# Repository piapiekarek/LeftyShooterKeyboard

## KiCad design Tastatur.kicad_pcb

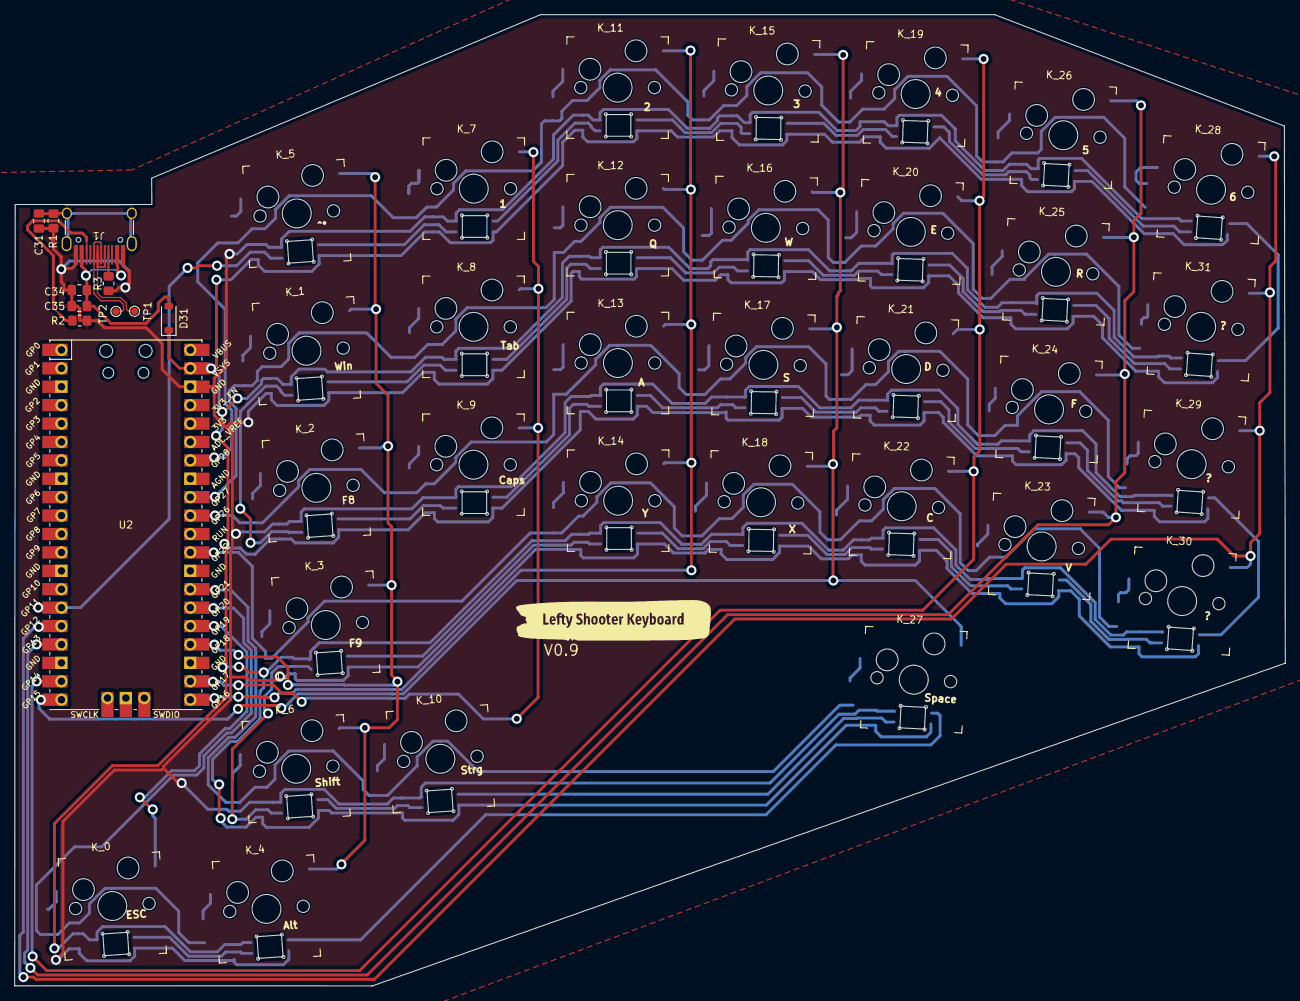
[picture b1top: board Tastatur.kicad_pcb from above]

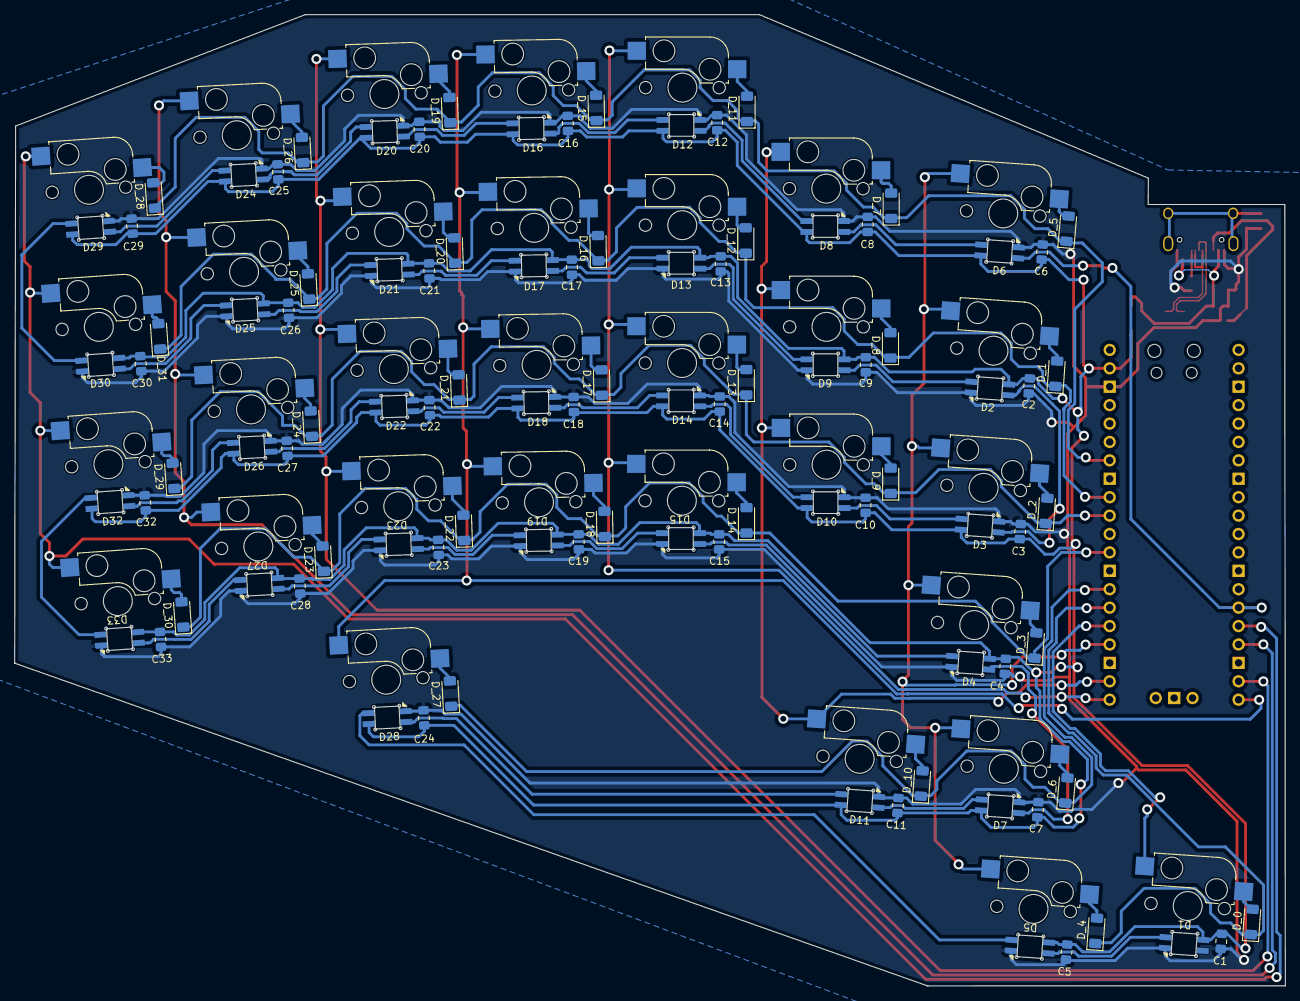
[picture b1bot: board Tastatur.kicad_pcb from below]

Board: 2 copper layers, 175.3 x 134.0 mm, 139 parts (96 on the bottom side), 56 nets.

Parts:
C1, C2, C3, C4, C5, C6, C7, C8, C9, C10, C11, C12, C13, C14, C15, C16, C17, C18, C19, C20, C21, C22, C23, C24, C25, C26, C27, C28, C29, C30, C32, C33, C35: 100n; C_0805_2012Metric_Pad1.18x1.45mm_HandSolder
C31: 20pF; C_0805_2012Metric_Pad1.18x1.45mm_HandSolder
C34: 1u; C_0805_2012Metric_Pad1.18x1.45mm_HandSolder
D1, D2, D3, D4, D5, D6, D7, D8, D9, D10, D11, D12, D13, D14, D15, D16, D17, D18, D19, D20, D21, D22, D23, D24, D25, D26, D27, D28, D29, D30, D32, D33: SK6812MINI; SK6803-MINI-E_pia
D31: 1N5817; D_SOD-123
D_0, D_1, D_2, D_3, D_4, D_5, D_6, D_7, D_8, D_9, D_10, D_11, D_12, D_13, D_14, D_15, D_16, D_17, D_18, D_19, D_20, D_21, D_22, D_23, D_24, D_25, D_26, D_27, D_28, D_29, D_30, D_31: D; D_MiniMELF
J1: USB_C_Receptacle_USB2.0_16P; USB-C Receptacle
K_0, K_1, K_2, K_3, K_4, K_5, K_6, K_7, K_8, K_9, K_10, K_11, K_12, K_13, K_14, K_15, K_16, K_17, K_18, K_19, K_20, K_21, K_22, K_23, K_24, K_25, K_26, K_27, K_28, K_29, K_30, K_31: KEYSW; Kailh_socket_MX_optional_pia
R1: 1M; R_0805_2012Metric_Pad1.20x1.40mm_HandSolder
R2, R3: 5K1; R_0805_2012Metric_Pad1.20x1.40mm_HandSolder
TP1, TP2: TestPoint; TestPoint_Pad_D1.0mm
U2: Pico; RPi_Pico_SMD_TH

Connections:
+5V: C1.1, C2.1, C3.1, C4.1, C5.1, C6.1, C7.1, C8.1, C9.1, C10.1, C11.1, C12.1, C13.1, C14.1, C15.1, C16.1, C17.1, C18.1, C19.1, C20.1, C21.1, C22.1, C23.1, C24.1, C25.1, C26.1, C27.1, C28.1, C29.1, C30.1, C32.1, C33.1, D1.4 (VDD), D2.4 (VDD), D3.4 (VDD), D4.4 (VDD), D5.4 (VDD), D6.4 (VDD), D7.4 (VDD), D8.4 (VDD), D9.4 (VDD), D10.4 (VDD), D11.4 (VDD), D12.4 (VDD), D13.4 (VDD), D14.4 (VDD), D15.4 (VDD), D16.4 (VDD), D17.4 (VDD), D18.4 (VDD), D19.4 (VDD), D20.4 (VDD), D21.4 (VDD), D22.4 (VDD), D23.4 (VDD), D24.4 (VDD), D25.4 (VDD), D26.4 (VDD), D27.4 (VDD), D28.4 (VDD), D29.4 (VDD), D30.4 (VDD), D31.1 (K), D32.4 (VDD), D33.4 (VDD), U2.39 (VSYS)
DM: J1.A7 (D-), J1.B7 (D-), TP1.1
DP: J1.A6 (D+), J1.B6 (D+), TP2.1
GND: C1.2, C2.2, C3.2, C4.2, C5.2, C6.2, C7.2, C8.2, C9.2, C10.2, C11.2, C12.2, C13.2, C14.2, C15.2, C16.2, C17.2, C18.2, C19.2, C20.2, C21.2, C22.2, C23.2, C24.2, C25.2, C26.2, C27.2, C28.2, C29.2, C30.2, C31.2, C32.2, C33.2, C34.2, C35.2, D1.2 (VSS), D2.2 (VSS), D3.2 (VSS), D4.2 (VSS), D5.2 (VSS), D6.2 (VSS), D7.2 (VSS), D8.2 (VSS), D9.2 (VSS), D10.2 (VSS), D11.2 (VSS), D12.2 (VSS), D13.2 (VSS), D14.2 (VSS), D15.2 (VSS), D16.2 (VSS), D17.2 (VSS), D18.2 (VSS), D19.2 (VSS), D20.2 (VSS), D21.2 (VSS), D22.2 (VSS), D23.2 (VSS), D24.2 (VSS), D25.2 (VSS), D26.2 (VSS), D27.2 (VSS), D28.2 (VSS), D29.2 (VSS), D30.2 (VSS), D32.2 (VSS), D33.2 (VSS), J1.A1 (GND), J1.A12 (GND), J1.B1 (GND), J1.B12 (GND), R1.2, R2.2, R3.2, U2.38 (GND)
LED: D6.3 (DIN), U2.15 (GPIO11)
unnamed: D1.3 (DIN), D5.1 (DOUT)
unnamed: D2.3 (DIN), D9.1 (DOUT)
unnamed: D2.1 (DOUT), D3.3 (DIN)
unnamed: D4.1 (DOUT), D7.3 (DIN)
unnamed: D6.1 (DOUT), D8.3 (DIN)
unnamed: D3.1 (DOUT), D10.3 (DIN)
unnamed: D10.1 (DOUT), D14.3 (DIN)
unnamed: D7.1 (DOUT), D11.3 (DIN)
unnamed: D11.1 (DOUT), D28.3 (DIN)
unnamed: D8.1 (DOUT), D12.3 (DIN)
unnamed: D12.1 (DOUT), D16.3 (DIN)
unnamed: D13.3 (DIN), D17.1 (DOUT)
unnamed: D9.3 (DIN), D13.1 (DOUT)
unnamed: D14.1 (DOUT), D18.3 (DIN)
unnamed: D15.3 (DIN), D19.1 (DOUT)
unnamed: D4.3 (DIN), D15.1 (DOUT)
unnamed: D16.1 (DOUT), D20.3 (DIN)
unnamed: D17.3 (DIN), D21.1 (DOUT)
unnamed: D18.1 (DOUT), D22.3 (DIN)
unnamed: D19.3 (DIN), D23.1 (DOUT)
unnamed: D20.1 (DOUT), D24.3 (DIN)
unnamed: D21.3 (DIN), D25.1 (DOUT)
unnamed: D22.1 (DOUT), D26.3 (DIN)
unnamed: D23.3 (DIN), D27.1 (DOUT)
unnamed: D24.1 (DOUT), D29.3 (DIN)
unnamed: D25.3 (DIN), D30.1 (DOUT)
unnamed: D26.1 (DOUT), D32.3 (DIN)
unnamed: D27.3 (DIN), D33.1 (DOUT)
unnamed: D5.3 (DIN), D28.1 (DOUT)
unnamed: D29.1 (DOUT), D30.3 (DIN)
unnamed: D32.1 (DOUT), D33.3 (DIN)
unnamed: D_3.2 (A), K_3.2 (ROW)
unnamed: D_12.2 (A), K_12.2 (ROW)
unnamed: J1.A5 (CC1), R3.1
unnamed: J1.B5 (CC2), R2.1
unnamed: C31.1, J1.S1 (SHIELD), R1.1
VBUS: C34.1, C35.1, D31.2 (A), J1.A4 (VBUS), J1.A9 (VBUS), J1.B4 (VBUS), J1.B9 (VBUS)
col0: K_0.1 (COL), U2.25 (GPIO19)
col1: K_1.1 (COL), K_2.1 (COL), K_3.1 (COL), K_4.1 (COL), K_5.1 (COL), K_6.1 (COL), U2.24 (GPIO18)
col2: K_7.1 (COL), K_8.1 (COL), K_9.1 (COL), K_10.1 (COL), U2.22 (GPIO17)
col3: K_11.1 (COL), K_12.1 (COL), K_13.1 (COL), K_14.1 (COL), U2.21 (GPIO16)
col4: K_15.1 (COL), K_16.1 (COL), K_17.1 (COL), K_18.1 (COL), K_27.1 (COL), U2.20 (GPIO15)
col5: K_19.1 (COL), K_20.1 (COL), K_21.1 (COL), K_22.1 (COL), U2.19 (GPIO14)
col6: K_23.1 (COL), K_24.1 (COL), K_25.1 (COL), K_26.1 (COL), U2.17 (GPIO13)
col7: K_28.1 (COL), K_29.1 (COL), K_30.1 (COL), K_31.1 (COL), U2.16 (GPIO12)
row0: D_5.1 (K), D_7.1 (K), D_11.1 (K), D_15.1 (K), D_19.1 (K), D_26.1 (K), D_28.1 (K), U2.34 (GPIO28_ADC2)
row1: D_1.1 (K), D_8.1 (K), D_12.1 (K), D_16.1 (K), D_20.1 (K), D_25.1 (K), D_31.1 (K), U2.32 (GPIO27_ADC1)
row2: D_2.1 (K), D_9.1 (K), D_13.1 (K), D_17.1 (K), D_21.1 (K), D_24.1 (K), D_29.1 (K), U2.31 (GPIO26_ADC0)
row3: D_3.1 (K), D_14.1 (K), D_18.1 (K), D_22.1 (K), D_23.1 (K), D_30.1 (K), U2.29 (GPIO22)
row4: D_6.1 (K), D_10.1 (K), D_27.1 (K), U2.27 (GPIO21)
row5: D_0.1 (K), D_4.1 (K), U2.26 (GPIO20)

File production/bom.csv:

Designator,Footprint,Quantity,Value,LCSC Part #
"C1, C10, C11, C12, C13, C14, C15, C16, C17, C18, C19, C2, C20, C21, C22, C23, C24, C25, C26, C27, C28, C29, C3, C30, C32, C33, C35, C4, C5, C6, C7, C8, C9",0805,33,100n,
C31,0805,1,20pF,
C34,0805,1,1u,
"D1, D10, D11, D12, D13, D14, D15, D16, D17, D18, D19, D2, D20, D21, D22, D23, D24, D25, D26, D27, D28, D29, D3, D30, D32, D33, D4, D5, D6, D7, D8, D9",SK6803-MINI-E_pia,32,SK6812MINI,
D31,D_SOD-123,1,1N5817,
"D_0, D_1, D_10, D_11, D_12, D_13, D_14, D_15, D_16, D_17, D_18, D_19, D_2, D_20, D_21, D_22, D_23, D_24, D_25, D_26, D_27, D_28, D_29, D_3, D_30, D_31, D_4, D_5, D_6, D_7, D_8, D_9",D_MiniMELF,32,D,
J1,USB-C Receptacle,1,USB_C_Receptacle_USB2.0_16P,
"K_0, K_1, K_10, K_11, K_12, K_13, K_14, K_15, K_16, K_17, K_18, K_19, K_2, K_20, K_21, K_22, K_23, K_24, K_25, K_26, K_27, K_28, K_29, K_3, K_30, K_31, K_4, K_5, K_6, K_7, K_8, K_9",Kailh_socket_MX_optional_pia,32,KEYSW,
R1,0805,1,1M,
"R2, R3",0805,2,5K1,
"TP1, TP2",TestPoint_Pad_D1.0mm,2,TestPoint,
U2,RPi_Pico_SMD_TH,1,Pico,

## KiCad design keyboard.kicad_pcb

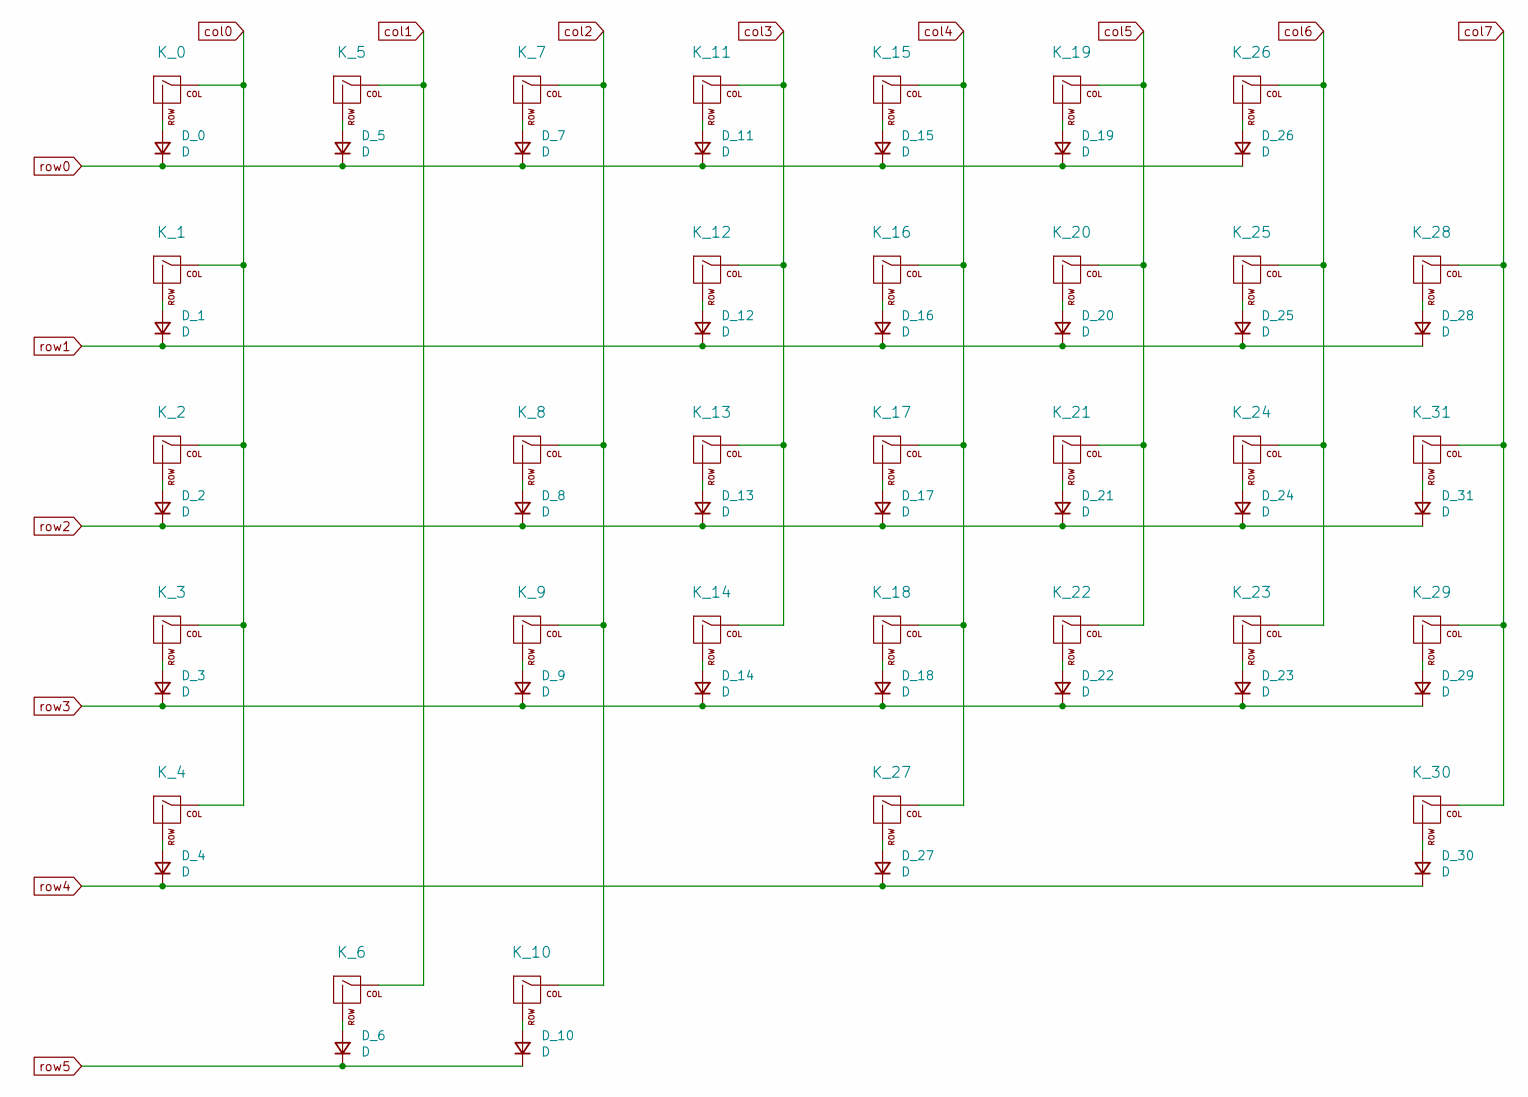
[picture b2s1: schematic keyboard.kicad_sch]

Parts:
D_0, D_1, D_2, D_3, D_4, D_5, D_6, D_7, D_8, D_9, D_10, D_11, D_12, D_13, D_14, D_15, D_16, D_17, D_18, D_19, D_20, D_21, D_22, D_23, D_24, D_25, D_26, D_27, D_28, D_29, D_30, D_31: D; D_SOD-123
K_0, K_2, K_3, K_5, K_7, K_11, K_12, K_13, K_14, K_15, K_16, K_17, K_18, K_19, K_20, K_21, K_22, K_23, K_24, K_25, K_26, K_28, K_29, K_30, K_31: KEYSW; MX-1U-NoLED
K_1, K_4, K_6, K_10: KEYSW; MX-1.25U-NoLED
K_8: KEYSW; MX-1.5U-NoLED
K_9: KEYSW; MX-1.75U-NoLED
K_27: KEYSW; MX-2.25U-NoLED

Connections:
unnamed: D_0.2 (A), K_0.2 (ROW)
unnamed: D_1.2 (A), K_1.2 (ROW)
unnamed: D_2.2 (A), K_2.2 (ROW)
unnamed: D_3.2 (A), K_3.2 (ROW)
unnamed: D_4.2 (A), K_4.2 (ROW)
unnamed: D_5.2 (A), K_5.2 (ROW)
unnamed: D_6.2 (A), K_6.2 (ROW)
unnamed: D_7.2 (A), K_7.2 (ROW)
unnamed: D_8.2 (A), K_8.2 (ROW)
unnamed: D_9.2 (A), K_9.2 (ROW)
unnamed: D_10.2 (A), K_10.2 (ROW)
unnamed: D_11.2 (A), K_11.2 (ROW)
unnamed: D_12.2 (A), K_12.2 (ROW)
unnamed: D_13.2 (A), K_13.2 (ROW)
unnamed: D_14.2 (A), K_14.2 (ROW)
unnamed: D_15.2 (A), K_15.2 (ROW)
unnamed: D_16.2 (A), K_16.2 (ROW)
unnamed: D_17.2 (A), K_17.2 (ROW)
unnamed: D_18.2 (A), K_18.2 (ROW)
unnamed: D_19.2 (A), K_19.2 (ROW)
unnamed: D_20.2 (A), K_20.2 (ROW)
unnamed: D_21.2 (A), K_21.2 (ROW)
unnamed: D_22.2 (A), K_22.2 (ROW)
unnamed: D_23.2 (A), K_23.2 (ROW)
unnamed: D_24.2 (A), K_24.2 (ROW)
unnamed: D_25.2 (A), K_25.2 (ROW)
unnamed: D_26.2 (A), K_26.2 (ROW)
unnamed: D_27.2 (A), K_27.2 (ROW)
unnamed: D_28.2 (A), K_28.2 (ROW)
unnamed: D_29.2 (A), K_29.2 (ROW)
unnamed: D_30.2 (A), K_30.2 (ROW)
unnamed: D_31.2 (A), K_31.2 (ROW)
col0: K_0.1 (COL), K_1.1 (COL), K_2.1 (COL), K_3.1 (COL), K_4.1 (COL)
col1: K_5.1 (COL), K_6.1 (COL)
col2: K_7.1 (COL), K_8.1 (COL), K_9.1 (COL), K_10.1 (COL)
col3: K_11.1 (COL), K_12.1 (COL), K_13.1 (COL), K_14.1 (COL)
col4: K_15.1 (COL), K_16.1 (COL), K_17.1 (COL), K_18.1 (COL), K_27.1 (COL)
col5: K_19.1 (COL), K_20.1 (COL), K_21.1 (COL), K_22.1 (COL)
col6: K_23.1 (COL), K_24.1 (COL), K_25.1 (COL), K_26.1 (COL)
col7: K_28.1 (COL), K_29.1 (COL), K_30.1 (COL), K_31.1 (COL)
row0: D_0.1 (K), D_5.1 (K), D_7.1 (K), D_11.1 (K), D_15.1 (K), D_19.1 (K), D_26.1 (K)
row1: D_1.1 (K), D_12.1 (K), D_16.1 (K), D_20.1 (K), D_25.1 (K), D_28.1 (K)
row2: D_2.1 (K), D_8.1 (K), D_13.1 (K), D_17.1 (K), D_21.1 (K), D_24.1 (K), D_31.1 (K)
row3: D_3.1 (K), D_9.1 (K), D_14.1 (K), D_18.1 (K), D_22.1 (K), D_23.1 (K), D_29.1 (K)
row4: D_4.1 (K), D_27.1 (K), D_30.1 (K)
row5: D_6.1 (K), D_10.1 (K)

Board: 2 copper layers, 64 parts (32 on the bottom side), 46 nets, no tracks yet.

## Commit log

2024-09-21 minor changes
2024-09-21 change dm dp
2024-09-25 changes mage
